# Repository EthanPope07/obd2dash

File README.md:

# OBD2Dash

An ESP32-S3 CAN-to-BLE bridge for an iPad vehicle dashboard. The firmware discovers each ECU's supported current-data PIDs and forwards complete raw responses through a versioned BLE GATT stream.

## Status

The original reader was a breadboard diagnostic sketch. This revision replaces its receive path and adds supported-PID discovery, ISO-TP reassembly and BLE. The new firmware has host regression tests; vehicle and iPad integration testing are still required. Do not represent the new implementation as vehicle-validated yet.

The PCB is a compact prototype, not a fabrication-qualified automotive module. See hardware/Review.md for the supplied review and its unresolved decoupling, component-selection and power-protection findings. That report is preserved as source evidence, not a new electrical signoff.

## Scope of "all PIDs"

- Service 01 (current powertrain data), PID 00 through FF.
- Every advertised support page, not a fixed shortlist of dashboard sensors.
- Separate support maps and responses for eight physical ECU addresses.
- Classical CAN with 11-bit IDs: requests 7E0–7E7, responses 7E8–7EF.
- 500 kbit/s by default; configurable 250 kbit/s.
- Raw response preservation, including multi-frame PIDs. The dashboard applies PID-specific formulas.
- Not manufacturer-specific services, all OBD diagnostic modes, 29-bit CAN, CAN FD, or legacy K-line/J1850.

A vehicle cannot return a PID it does not implement. A discovery timeout is reported as incomplete, not silently interpreted as no support.

## Data flow

CAN request -> ECU response -> ISO-TP reassembly -> timestamped raw PID record -> 20-byte BLE fragments -> iPad reassembly and decoding.

There is one outstanding physical request at a time. All supported data PIDs are polled round-robin; support pages are refreshed between sweeps after at least 60 seconds. Requests have a 50 ms minimum gap, 300 ms inactivity timeout and 5-second absolute deadline. Discovery retries transient failures up to three times. Sample failures produce status records and are retried on later sweeps.

This prioritizes coverage rather than high-rate gauges: polling many PIDs or offline ECUs makes a sweep longer. No fixed update-rate guarantee is claimed.

## Hardware and build

The supplied PCB identifies ESP32-S3-WROOM-1 and TI TCAN337:
- GPIO4 -> TCAN337 TXD
- GPIO5 <- TCAN337 RXD

Confirm the external connector cable pinout and power design before connecting hardware. The firmware sends only Mode 01 requests and ISO-TP flow control; BLE provides no arbitrary CAN-write interface.

Open firmware/obd2dash/obd2dash.ino in Arduino IDE. Select ESP32S3 Dev Module using the Espressif ESP32 package. BLE and TWAI ship with that package. Configure pins and bitrate in Config.h. No WiFi credentials or cloud services are required.

    arduino-cli compile --fqbn esp32:esp32:esp32s3 firmware/obd2dash

## Repository

- firmware/obd2dash: request engine, protocol core and BLE stream
- docs/BLE.md: exact wire format and app integration
- tools/decode_ble.py: reference decoder for notification hex lines
- tests: host protocol and decoder regression tests
- hardware: supplied KiCad source, local footprints, DRC reports and previews

## Tests

    g++ -std=c++17 -Wall -Wextra -Werror tests/protocol_test.cpp -o protocol_test
    ./protocol_test
    python -m unittest discover -s tests -p "test_*.py"

The C++ tests exercise support-map boundaries, independent ECU maps, all 4,088 ISO-TP multi-frame lengths from 8 to 4,095 bytes, sequence rollover/errors, negative responses and maximum-length BLE serialization. Tests do not replace CAN simulator, vehicle or radio testing.

## References

- [Espressif BLE notification example](https://github.com/espressif/arduino-esp32/tree/master/libraries/BLE/examples/Notify)
- [ISO-TP transport overview](https://docs.kernel.org/networking/iso15765-2.html)
- [OBD support-page explanation](https://www.csselectronics.com/pages/obd2-explained-simple-intro)

## Verified build

Compiled successfully with Espressif Arduino-ESP32 3.3.11 (bundled BLE 3.3.11), target esp32:esp32:esp32s3, board defaults.

- Program storage: 576,620 / 1,310,720 bytes (43%).
- Static global RAM: 31,744 / 327,680 bytes (9%).
- Host C++ protocol regression suite: passed.
- Python BLE decoder suite: 4 tests passed.

No device was flashed. These compile figures do not measure peak runtime RAM. Vehicle/CAN simulator tests and iPad integration remain outstanding; follow docs/VALIDATION.md.

## iPad dashboard

The native SwiftUI receiving app is in [ipad](ipad/README.md). Open ipad/OBD2Dash.xcodeproj on a Mac, select your signing team and run on an iPad with iPadOS 17+. It automatically connects while foregrounded and displays RPM, speed and coolant gauges alongside a searchable list of supported/observed PIDs.

Unknown PIDs are shown as raw bytes, not guessed numbers. The app has an explicitly labeled --demo mode for UI previews. See the app README for build and physical-device validation instructions.

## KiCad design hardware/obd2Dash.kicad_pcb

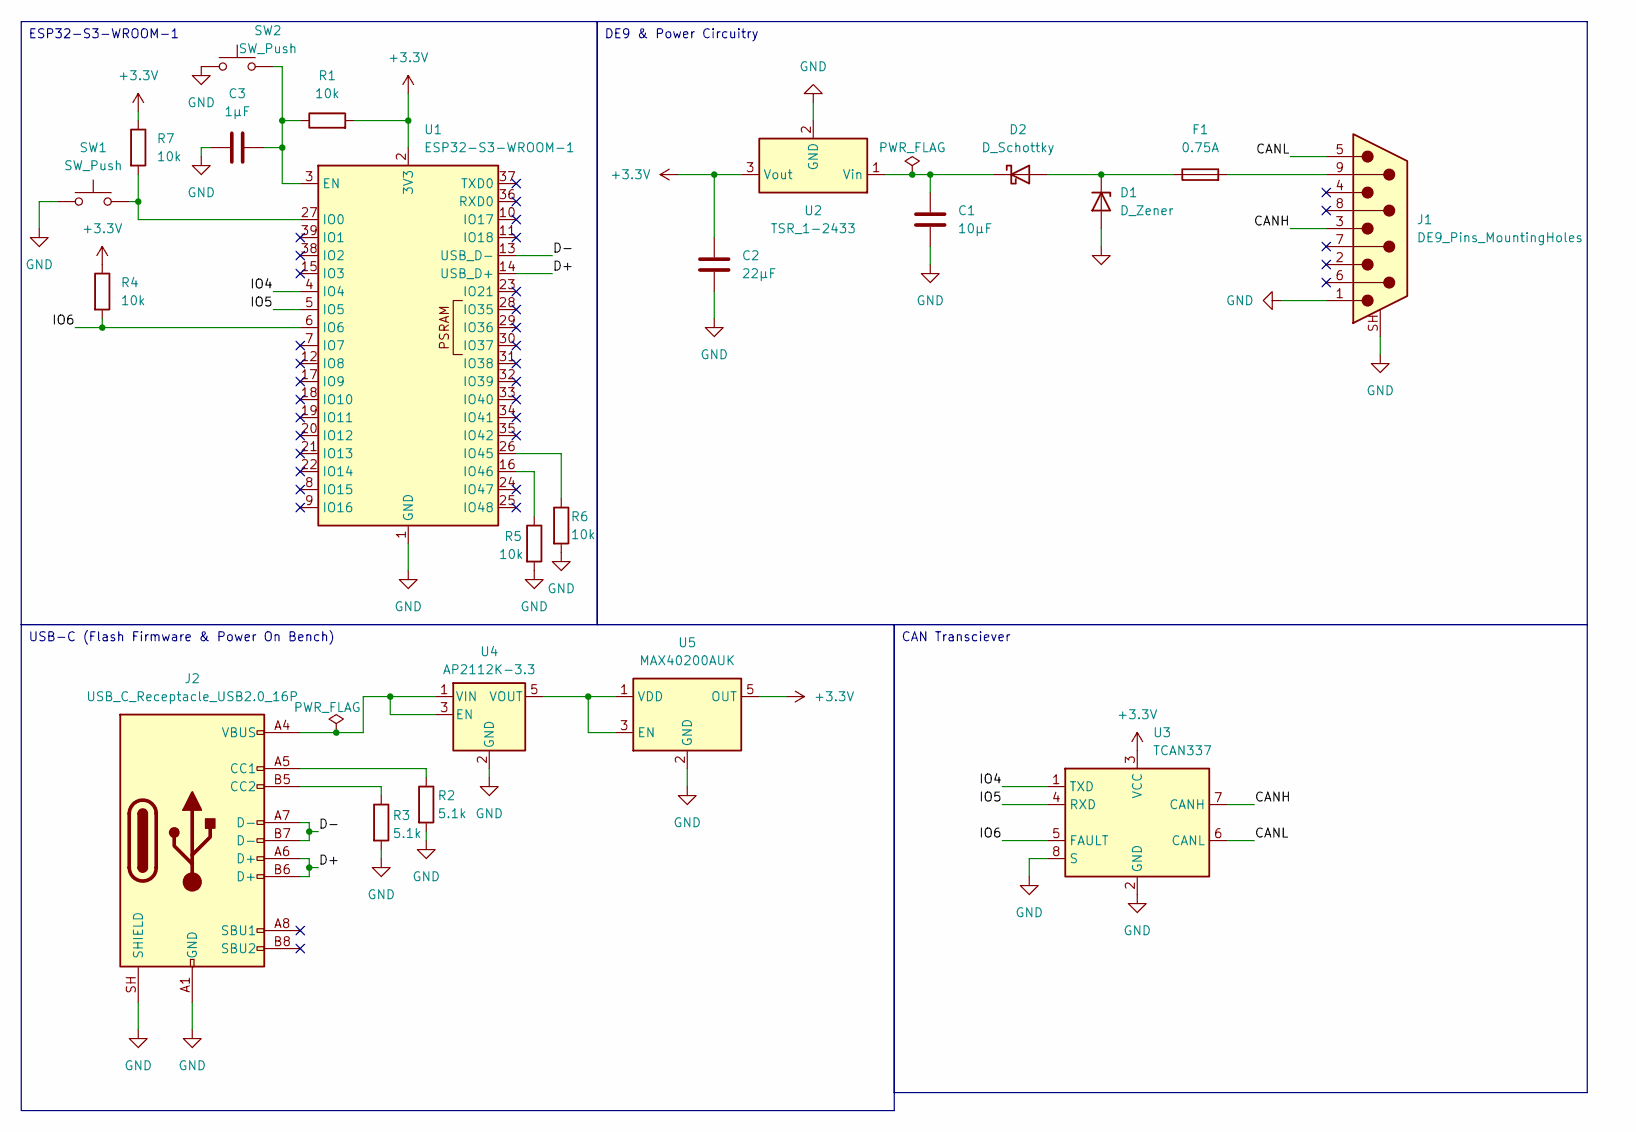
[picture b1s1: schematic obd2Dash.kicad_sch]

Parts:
C1: 10µF; C_1210_3225Metric_Pad1.33x2.70mm_HandSolder
C2: 22µF; C_1206_3216Metric_Pad1.33x1.80mm_HandSolder
C3: 1µF; C_0603_1608Metric
D1: D_Zener; D_SMB_Handsoldering
D2: D_Schottky; D_SMA_Handsoldering
F1: 0.75A; FUSE_1812L200_12DR
J1: DE9_Pins_MountingHoles; DSUB-9_Pins_Vertical_P2.77x2.84mm_MountingHoles
J2: USB_C_Receptacle_USB2.0_16P; USB_C_Receptacle_GCT_USB4085
R1, R4, R5, R6, R7: 10k; R_0603_1608Metric
R2, R3: 5.1k; R_0603_1608Metric
SW1, SW2: SW_Push; SW_PUSH_6mm_H4.3mm
U1: ESP32-S3-WROOM-1
U2: TSR_1-2433; Converter_DCDC_TRACO_TSR-1_THT
U3: TCAN337; SOIC-8_3.9x4.9mm_P1.27mm
U4: AP2112K-3.3; SOT-23-5
U5: MAX40200AUK; SOT-23-5

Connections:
+3.3V: C2.1, R1.2, R4.1, R7.1, U1.2 (3V3), U2.3 (Vout), U3.3 (VCC), U5.5 (OUT)
/CANH: J1.3, U3.7 (CANH)
/CANL: J1.5, U3.6 (CANL)
/D+: J2.A6 (D+), J2.B6 (D+), U1.14 (USB_D+)
/D-: J2.A7 (D-), J2.B7 (D-), U1.13 (USB_D-)
/IO4: U1.4 (IO4), U3.1 (TXD)
/IO5: U1.5 (IO5), U3.4 (RXD)
/IO6: R4.2, U1.6 (IO6), U3.5 (FAULT)
GND: C1.2, C2.2, C3.1, D1.2 (A), J1.1, J1.SH (PAD), J2.A1 (GND), J2.A12 (GND), J2.B1 (GND), J2.B12 (GND), J2.SH (SHIELD), R2.2, R3.2, R5.2, R6.2, SW1.1, SW2.1, U1.1 (GND), U1.40 (GND), U1.41 (GND), U2.2 (GND), U3.2 (GND), U3.8 (S), U4.2 (GND), U5.2 (GND)
unnamed: D1.1 (K), D2.2 (A), F1.1
unnamed: C1.1, D2.1 (K), U2.1 (Vin)
unnamed: F1.2, J1.9
unnamed: J2.A5 (CC1), R2.1
unnamed: J2.B5 (CC2), R3.1
unnamed: C3.2, R1.1, SW2.2, U1.3 (EN)
unnamed: R7.2, SW1.2, U1.27 (IO0)
unnamed: R6.1, U1.26 (IO45)
unnamed: R5.1, U1.16 (IO46)
unnamed: J2.A4 (VBUS), J2.A9 (VBUS), J2.B4 (VBUS), J2.B9 (VBUS), U4.1 (VIN), U4.3 (EN)
unnamed: U4.5 (VOUT), U5.1 (VDD), U5.3 (EN)

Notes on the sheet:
ESP32-S3-WROOM-1
CAN Transciever
DE9 & Power Circuitry
USB-C (Flash Firmware & Power On Bench)

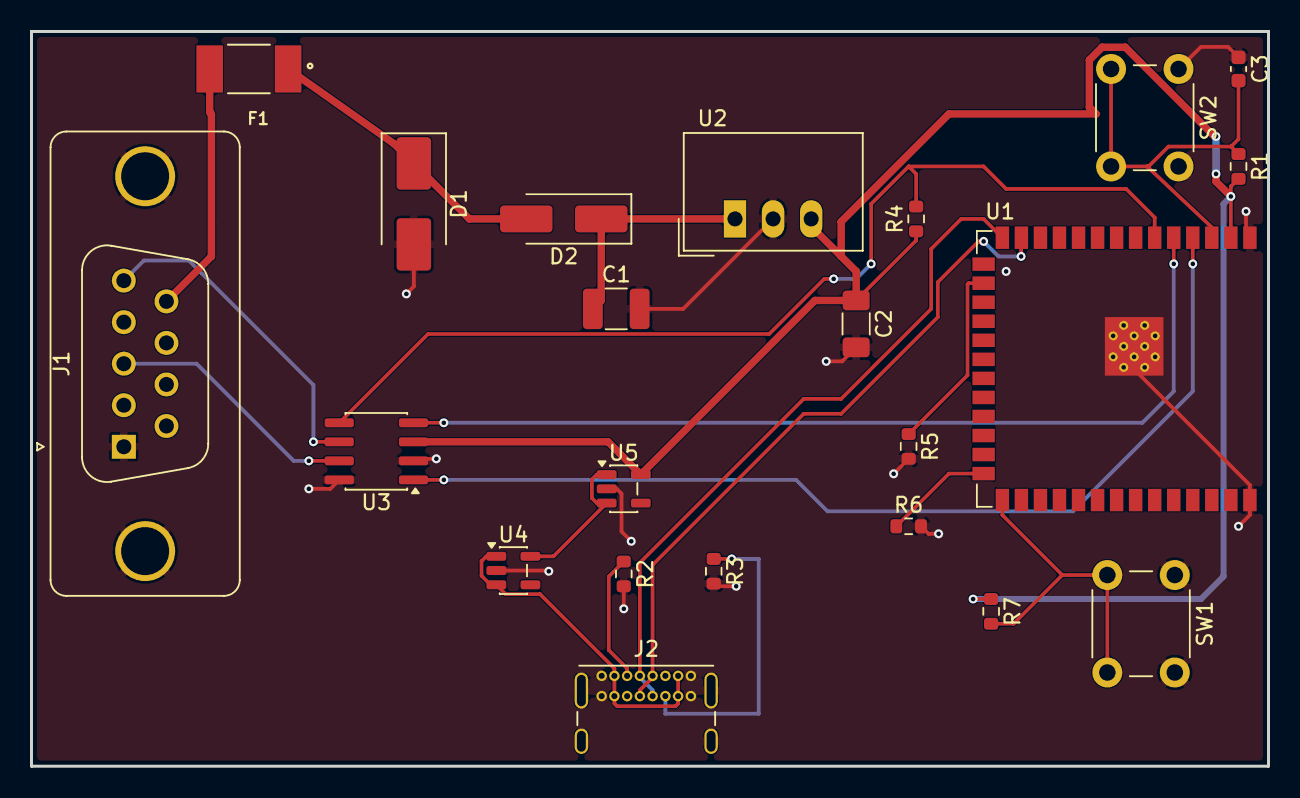
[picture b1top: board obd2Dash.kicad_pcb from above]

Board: 2 copper layers, 82.5 x 49.0 mm, 22 parts (0 on the bottom side), 20 nets.
